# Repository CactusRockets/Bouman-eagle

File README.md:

# Avionics Boards for the Bouman-3KM Rocket

This repository contains the design files for the avionics boards used in the **Bouman 3 km rocket**, developed by **Cactus Rockets Design**.

## Description

The avionics system is composed of the following boards:

- **COTS Board**
- **Processing Board**
- **Actuation Board**
- **Battery Board**

The **COTS Board** is responsible for measuring pressure, altitude, acceleration, and the rocket’s orientation.

The **Processing Board** handles the processing of data received from the COTS board and the GPS module, stores this data, and transmits it via telemetry.

The **Actuation Board** contains the circuitry required to correctly activate the squibs (skibs) used in the recovery system.

The **Battery Board** distributes the battery voltages to connectors so they can be easily used by the other boards.

> **Note:** All board files can be opened using **Autodesk Eagle** software.

## Schematics and Layouts

### COTS Board

### Processing Board

### Actuation Board

### Battery Board

## System Operation

Both the **COTS Board** and the **Processing Board** include activation switches. The system startup sequence is as follows:

1. Activate the switch on the COTS Board.
2. Activate the switch on the Processing Board.

After each sensor reading, the data is stored on a microSD card and transmitted via telemetry.

When the COTS board detects the rocket’s descent, it sends a signal to the Actuation Board, which then triggers the squib responsible for deploying the **drogue parachute**.

During the descent with only the drogue parachute deployed, once the rocket reaches an altitude below **500 meters**, the system detects this condition and activates the second squib. This action deploys the **main parachute**, ensuring a stable and controlled descent of the rocket until touchdown.

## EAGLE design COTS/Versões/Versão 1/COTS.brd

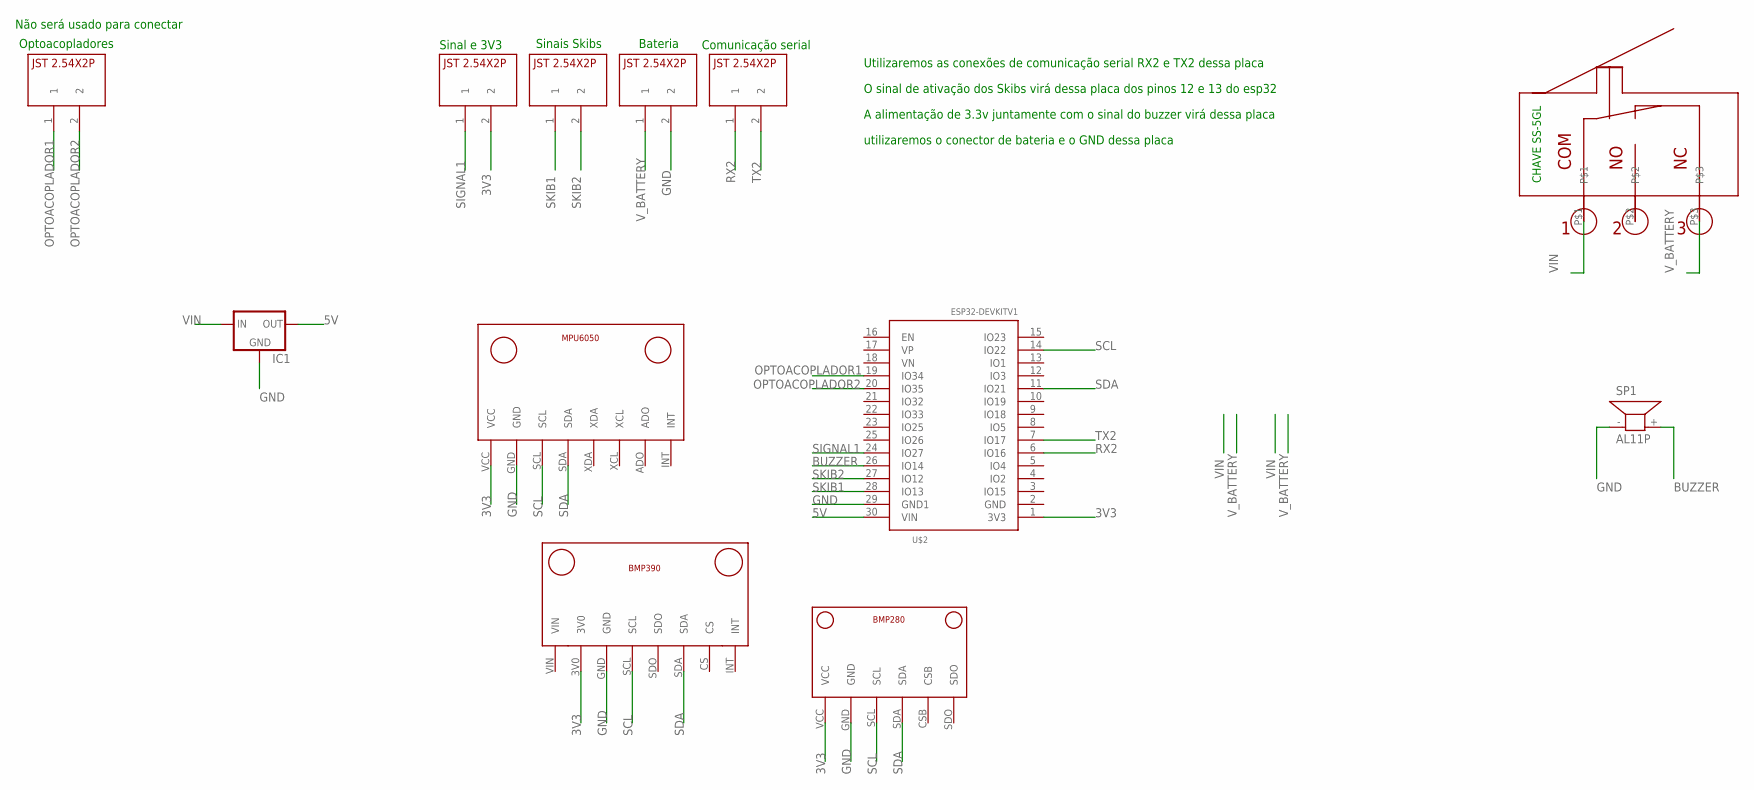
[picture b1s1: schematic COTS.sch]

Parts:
IC1: 78XXL
SP1: AL11P
U$1: MPU6050V1; MPU6050_FOOTPRINT
U$2: ESP32DEVKITV1; ESP32-DEVKITV1
U$3: BMP390V1; BMP390_FOOTPRINT
U$4, U$5, U$6, U$7, U$9: JST2.54X2P; JST2.54X2P_FOOTPRINT
U$8: CHAVE_SS-5GL; CHAVESS-5GL
U$10: BMP280V1; BMP280_FOOTPRINT

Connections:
3V3: U$1.VCC, U$2.1 (3V3), U$3.3V0, U$5.2, U$10.VCC
5V: IC1.OUT, U$2.30 (VIN)
BUZZER: SP1.+ (2), U$2.26 (IO14)
GND: IC1.GND, SP1.- (1), U$1.GND, U$2.29 (GND1), U$3.GND, U$6.2, U$10.GND
OPTOACOPLADOR1: U$2.19 (IO34), U$9.1
OPTOACOPLADOR2: U$2.20 (IO35), U$9.2
RX2: U$2.6 (IO16), U$7.1
SCL: U$1.SCL, U$2.14 (IO22), U$3.SCL, U$10.SCL
SDA: U$1.SDA, U$2.11 (IO21), U$3.SDA, U$10.SDA
SIGNAL1: U$2.24 (IO27), U$5.1
SKIB1: U$2.28 (IO13), U$4.1
SKIB2: U$2.27 (IO12), U$4.2
TX2: U$2.7 (IO17), U$7.2
VIN: IC1.IN, U$8.P$1
V_BATTERY: U$6.1, U$8.P$3

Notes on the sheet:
Sinais Skibs
Sinal e 3V3
Bateria
Comunicação serial
Optoacopladores
Utilizaremos as conexões de comunicação serial RX2 e TX2 dessa placa
O sinal de ativação dos Skibs virá dessa placa dos pinos 12 e 13 do esp32
A alimentação de 3.3v juntamente com o sinal do buzzer virá dessa placa
utilizaremos o conector de bateria e o GND dessa placa
Não será usado para conectar

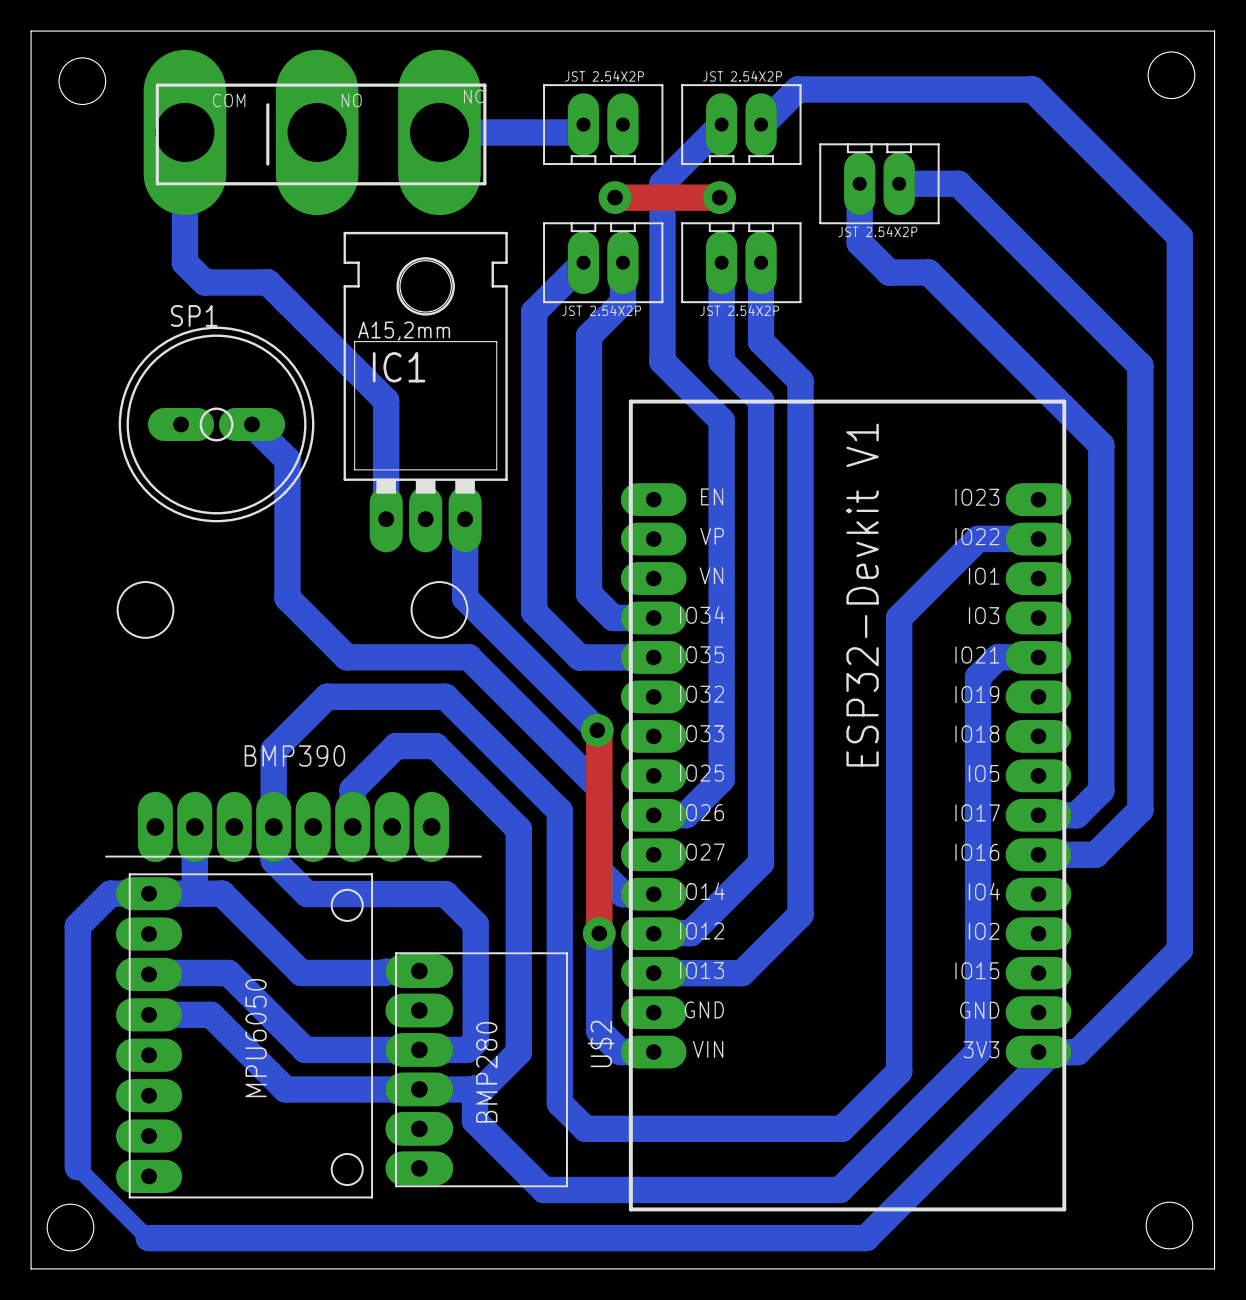
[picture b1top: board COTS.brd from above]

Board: 2 copper layers, 76.2 x 79.7 mm, 12 parts (0 on the bottom side), 15 nets.

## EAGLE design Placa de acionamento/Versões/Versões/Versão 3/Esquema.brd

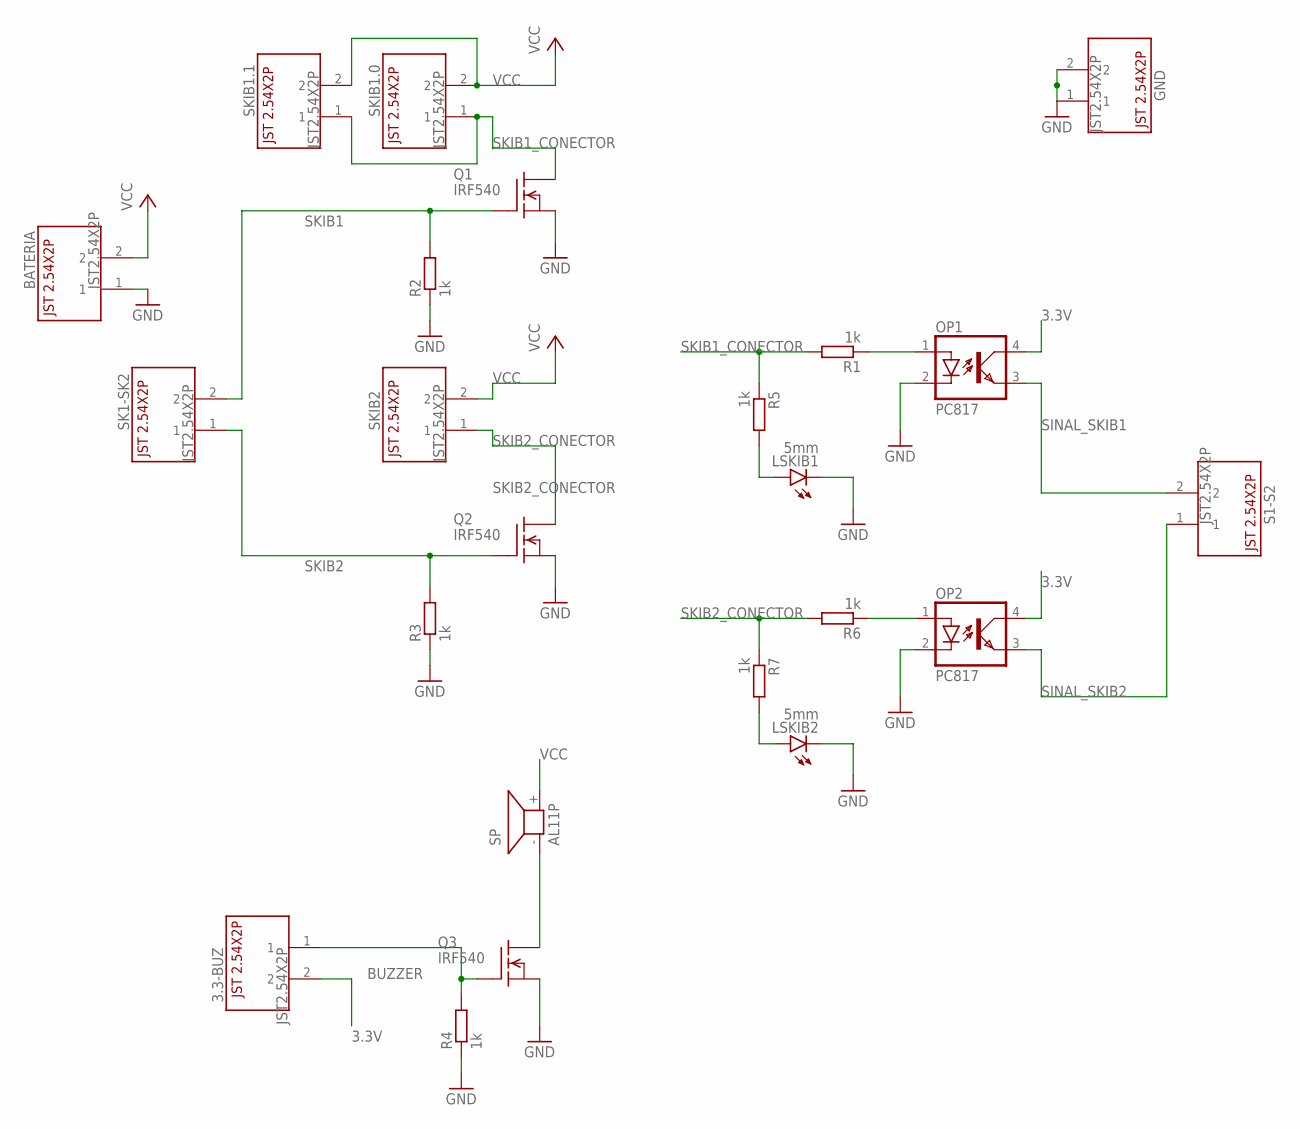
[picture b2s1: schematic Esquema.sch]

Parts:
3.3-BUZ: JST2.54X2P; JST2.54X2P_FOOTPRINT
BATERIA: JST2.54X2P; JST2.54X2P_FOOTPRINT
GND: JST2.54X2P; JST2.54X2P_FOOTPRINT
LSKIB1, LSKIB2: 5mm; LED5MM
OP1, OP2: PC817; DIL04
Q1, Q2, Q3: IRF540; TO220
R1, R2, R3, R4, R5, R6, R7: 1k; 0207/10
S1-S2: JST2.54X2P; JST2.54X2P_FOOTPRINT
SK1-SK2: JST2.54X2P; JST2.54X2P_FOOTPRINT
SKIB1.0, SKIB1.1, SKIB2: JST2.54X2P; JST2.54X2P_FOOTPRINT
SP: AL11P

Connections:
3.3V: 3.3-BUZ.2, OP1.4 (COL), OP2.4 (COL)
BUZZER: 3.3-BUZ.1, Q3.1 (G), R4.2
GND: BATERIA.1, GND.1, GND.2, LSKIB1.K (C), LSKIB2.K (C), OP1.2 (C), OP2.2 (C), Q1.3 (S), Q2.3 (S), Q3.3 (S), R2.1, R3.1, R4.1
unnamed: LSKIB2.A, R7.2
unnamed: Q3.2 (D), SP.- (1)
unnamed: LSKIB1.A, R5.2
unnamed: OP1.1 (A), R1.1
unnamed: OP2.1 (A), R6.1
SINAL_SKIB1: OP1.3 (EMIT), S1-S2.2
SINAL_SKIB2: OP2.3 (EMIT), S1-S2.1
SKIB1: Q1.1 (G), R2.2, SK1-SK2.2
SKIB1_CONECTOR: Q1.2 (D), R1.2, R5.1, SKIB1.0.1, SKIB1.1.1
SKIB2: Q2.1 (G), R3.2, SK1-SK2.1
SKIB2_CONECTOR: Q2.2 (D), R6.2, R7.1, SKIB2.1
VCC: BATERIA.2, SKIB1.0.2, SKIB1.1.2, SKIB2.2, SP.+ (2)

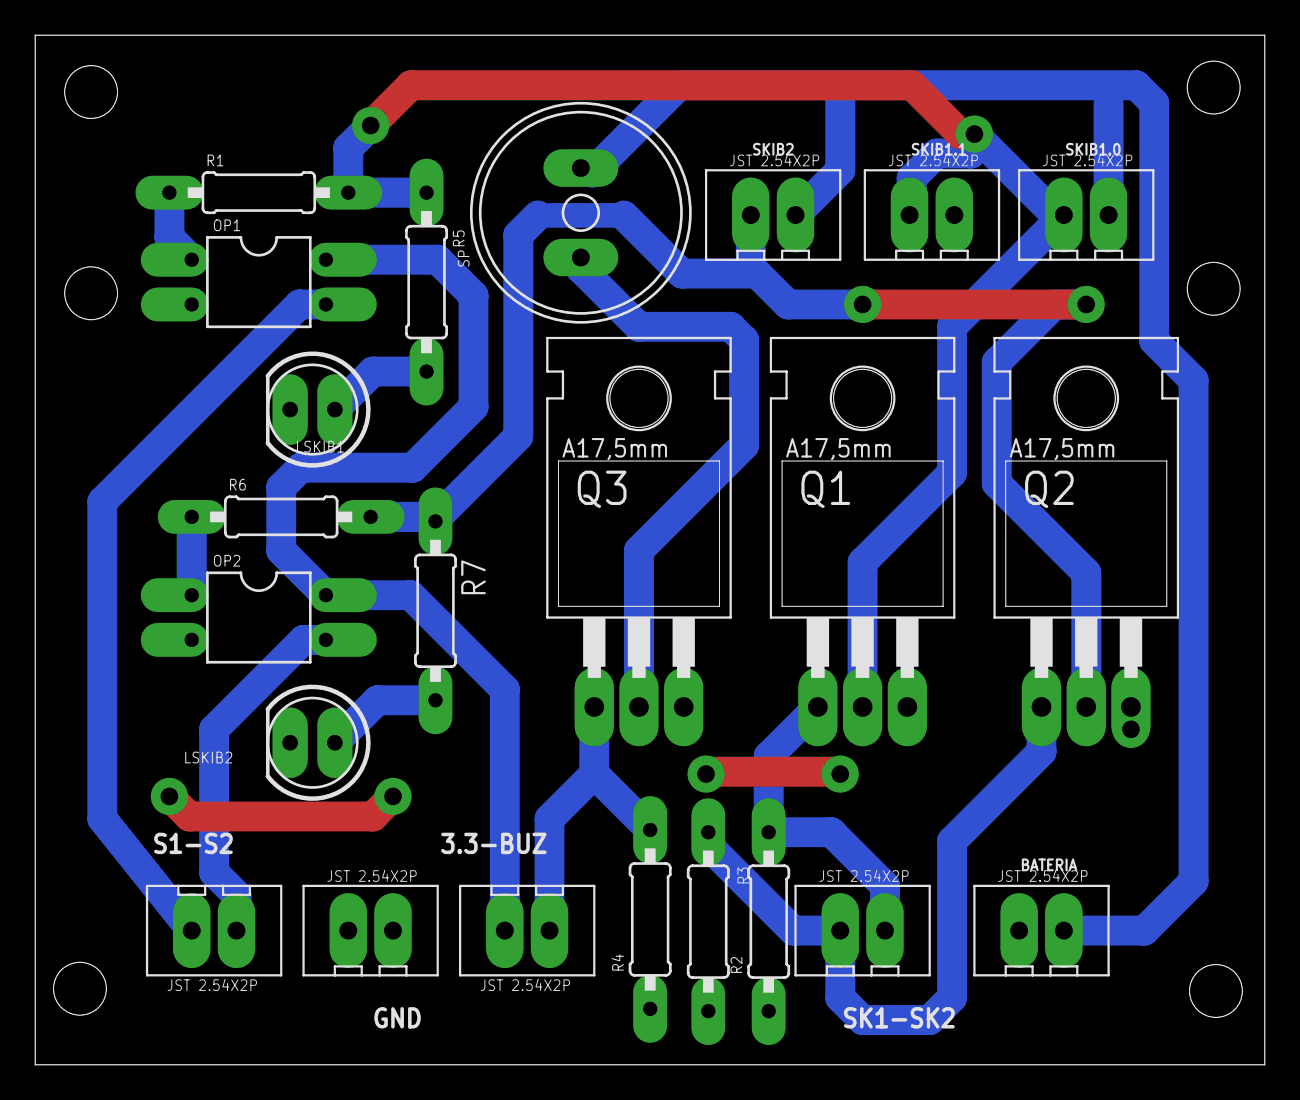
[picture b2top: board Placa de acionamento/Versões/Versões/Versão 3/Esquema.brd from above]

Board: 2 copper layers, 69.8 x 58.5 mm, 23 parts (0 on the bottom side), 15 nets.

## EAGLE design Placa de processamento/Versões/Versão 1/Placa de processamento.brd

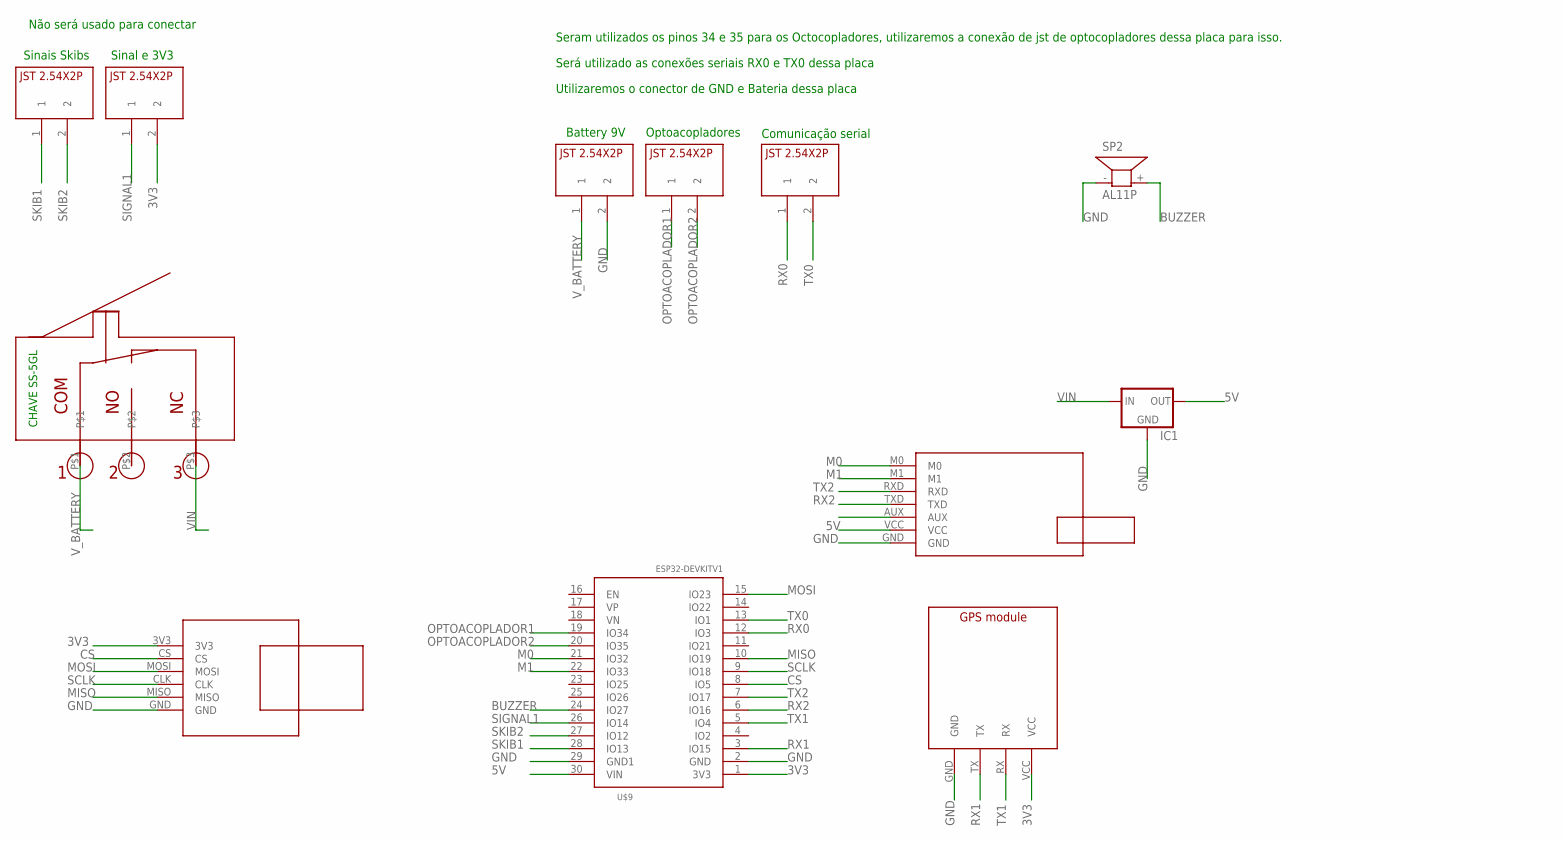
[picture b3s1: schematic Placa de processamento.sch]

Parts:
IC1: 78XXL
SP2: AL11P
U$2: MICROSD_SMALL_READER; MICROSD_SMALL_READER_FOOTPRINT
U$3, U$4, U$5, U$6, U$10: JST2.54X2P; JST2.54X2P_FOOTPRINT
U$7: GPS_MODULE; GPS_MODULE_FOOTPRINT
U$8: E22-400T30D; E22-400T30D_FOOTPRINT
U$9: ESP32DEVKITV1; ESP32-DEVKITV1
U$11: CHAVE_SS-5GL; CHAVESS-5GL

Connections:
3V3: U$2.3V3, U$5.2, U$7.VCC, U$9.1 (3V3)
5V: IC1.OUT, U$8.VCC, U$9.30 (VIN)
BUZZER: SP2.+ (2), U$9.24 (IO27)
CS: U$2.CS, U$9.8 (IO5)
GND: IC1.GND, SP2.- (1), U$2.GND, U$3.2, U$7.GND, U$8.GND, U$9.2 (GND), U$9.29 (GND1)
M0: U$8.M0, U$9.21 (IO32)
M1: U$8.M1, U$9.22 (IO33)
MISO: U$2.MISO, U$9.10 (IO19)
MOSI: U$2.MOSI, U$9.15 (IO23)
OPTOACOPLADOR1: U$6.1, U$9.19 (IO34)
OPTOACOPLADOR2: U$6.2, U$9.20 (IO35)
RX0: U$9.12 (IO3), U$10.1
RX1: U$7.TX, U$9.3 (IO15)
RX2: U$8.TXD, U$9.6 (IO16)
SCLK: U$2.CLK, U$9.9 (IO18)
SIGNAL1: U$5.1, U$9.26 (IO14)
SKIB1: U$4.1, U$9.28 (IO13)
SKIB2: U$4.2, U$9.27 (IO12)
TX0: U$9.13 (IO1), U$10.2
TX1: U$7.RX, U$9.5 (IO4)
TX2: U$8.RXD, U$9.7 (IO17)
VIN: IC1.IN, U$11.P$3
V_BATTERY: U$3.1, U$11.P$1

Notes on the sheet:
Battery 9V
Sinais Skibs
Sinal e 3V3
Optoacopladores
Comunicação serial
Seram utilizados os pinos 34 e 35 para os Octocopladores, utilizaremos a conexão de jst de optocopladores dessa placa para isso.
Será utilizado as conexões seriais RX0 e TX0 dessa placa
Utilizaremos o conector de GND e Bateria dessa placa
Não será usado para conectar

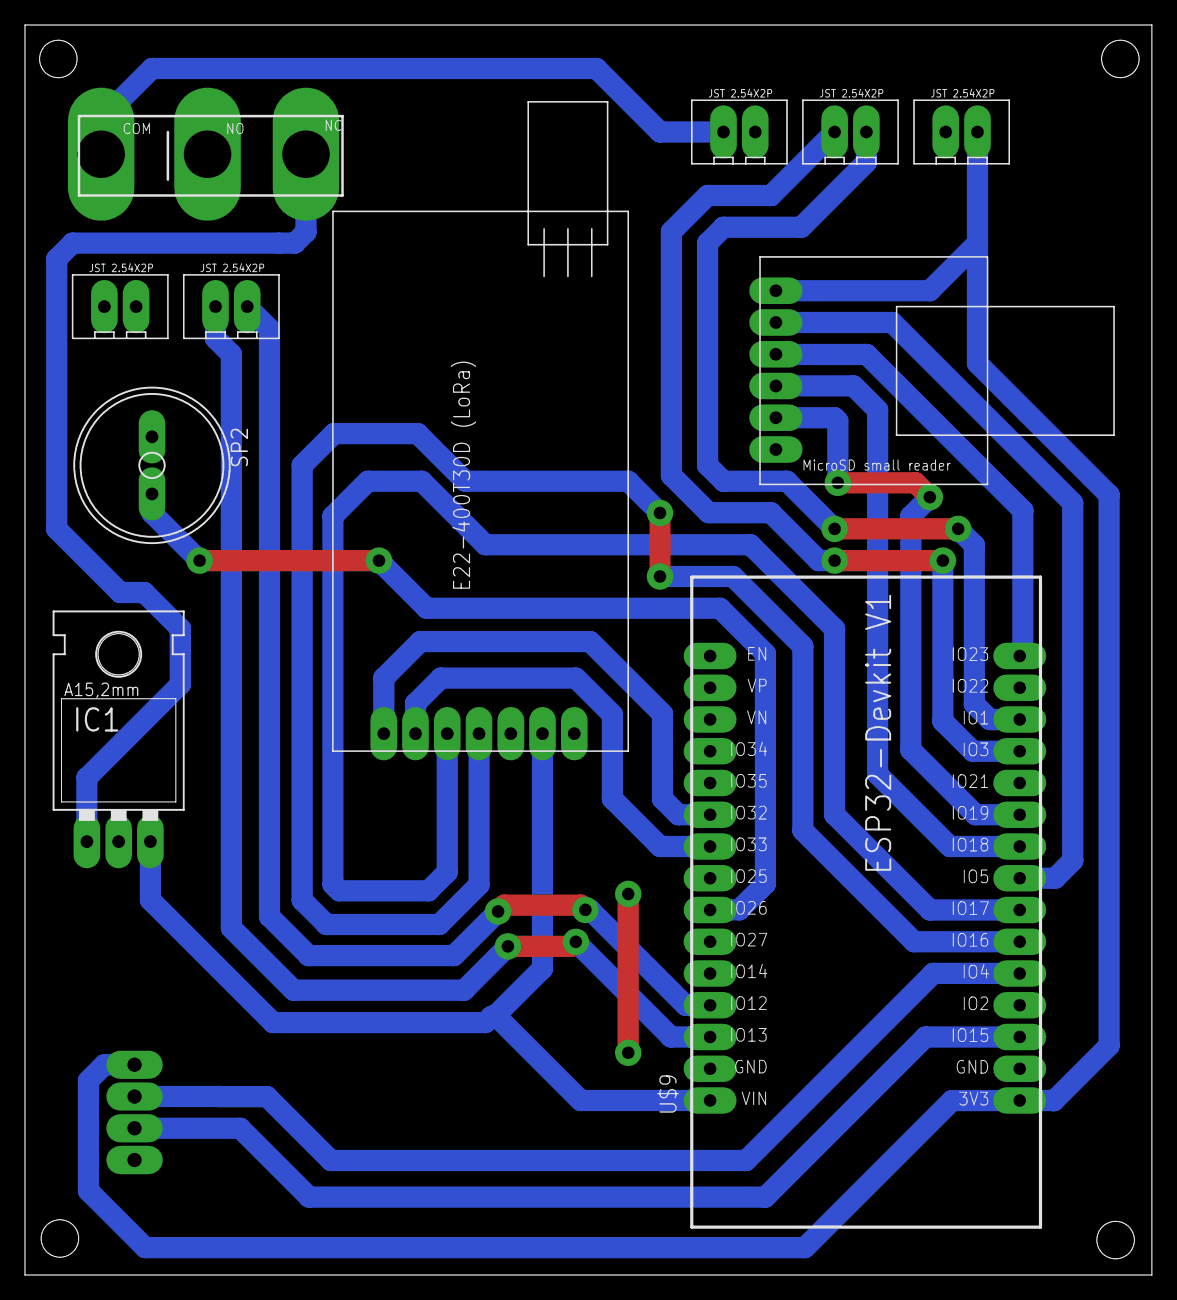
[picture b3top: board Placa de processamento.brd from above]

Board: 2 copper layers, 90.2 x 100.0 mm, 12 parts (1 on the bottom side), 23 nets.

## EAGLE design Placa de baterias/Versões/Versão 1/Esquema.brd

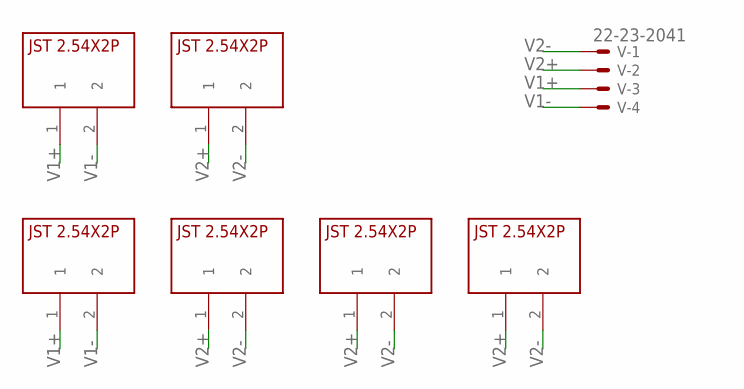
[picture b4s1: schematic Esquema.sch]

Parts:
U$1, U$2, U$3, U$4, U$5, U$6: JST2.54X2P; JST2.54X2P_FOOTPRINT
V: 22-23-2041

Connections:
V1+: U$1.1, U$4.1, V.3
V1-: U$1.2, U$4.2, V.4
V2+: U$2.1, U$3.1, U$5.1, U$6.1, V.2
V2-: U$2.2, U$3.2, U$5.2, U$6.2, V.1

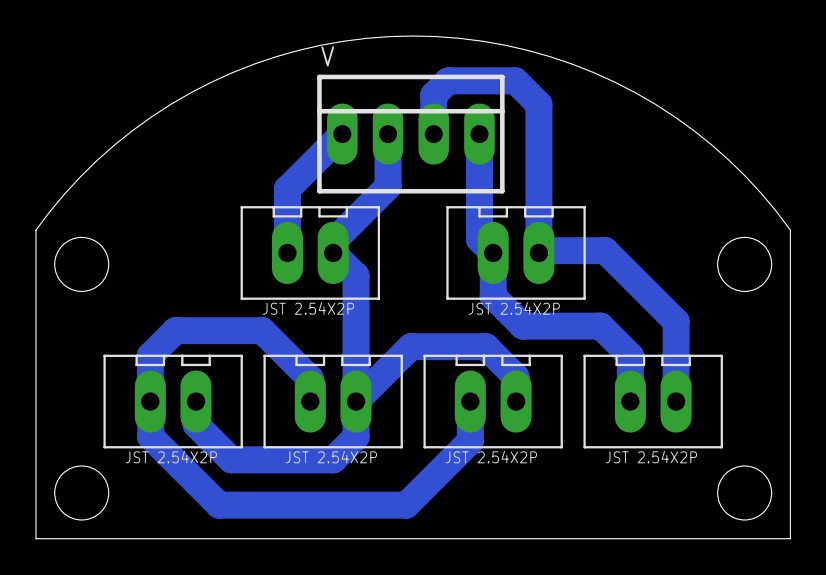
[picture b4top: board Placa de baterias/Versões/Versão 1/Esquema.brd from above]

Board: 2 copper layers, 41.9 x 27.9 mm, 7 parts (0 on the bottom side), 4 nets.

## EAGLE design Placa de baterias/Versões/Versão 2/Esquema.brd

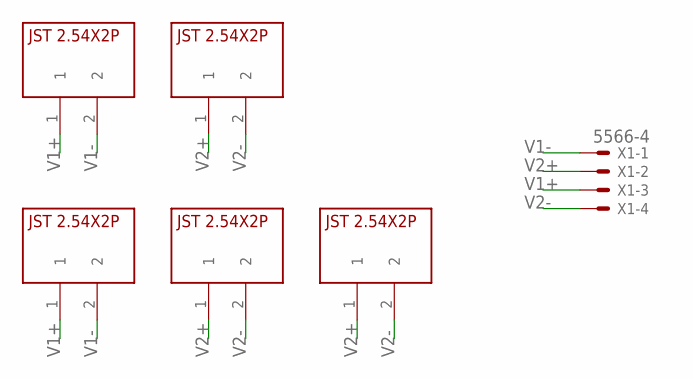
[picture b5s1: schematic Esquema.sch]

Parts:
U$1, U$2, U$3, U$4, U$5: JST2.54X2P; JST2.54X2P_FOOTPRINT
X1: 5566-4

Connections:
V1+: U$1.1, U$4.1, X1.3
V1-: U$1.2, U$4.2, X1.1
V2+: U$2.1, U$3.1, U$5.1, X1.2
V2-: U$2.2, U$3.2, U$5.2, X1.4

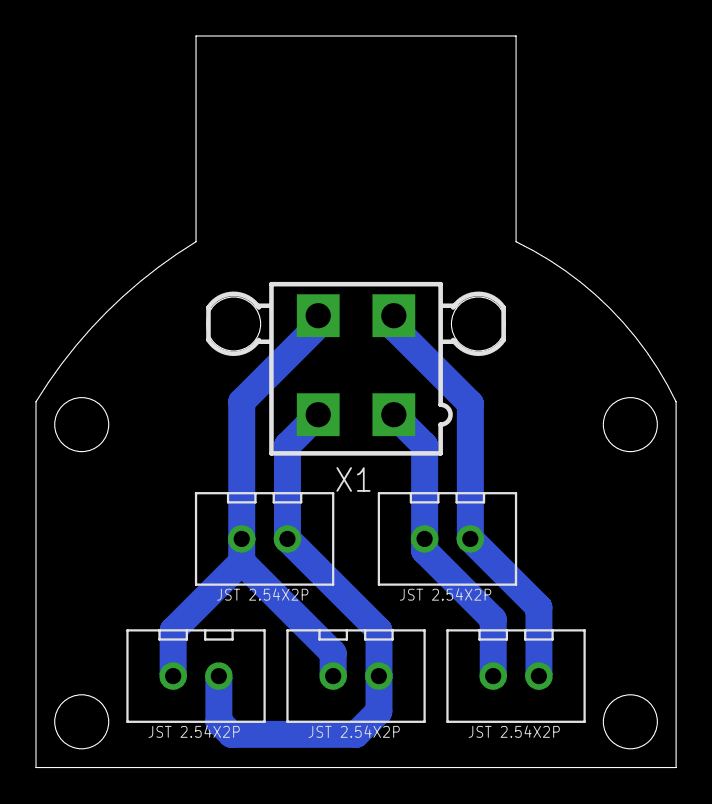
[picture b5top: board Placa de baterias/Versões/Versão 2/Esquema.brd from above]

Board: 2 copper layers, 35.6 x 40.6 mm, 6 parts (0 on the bottom side), 4 nets.

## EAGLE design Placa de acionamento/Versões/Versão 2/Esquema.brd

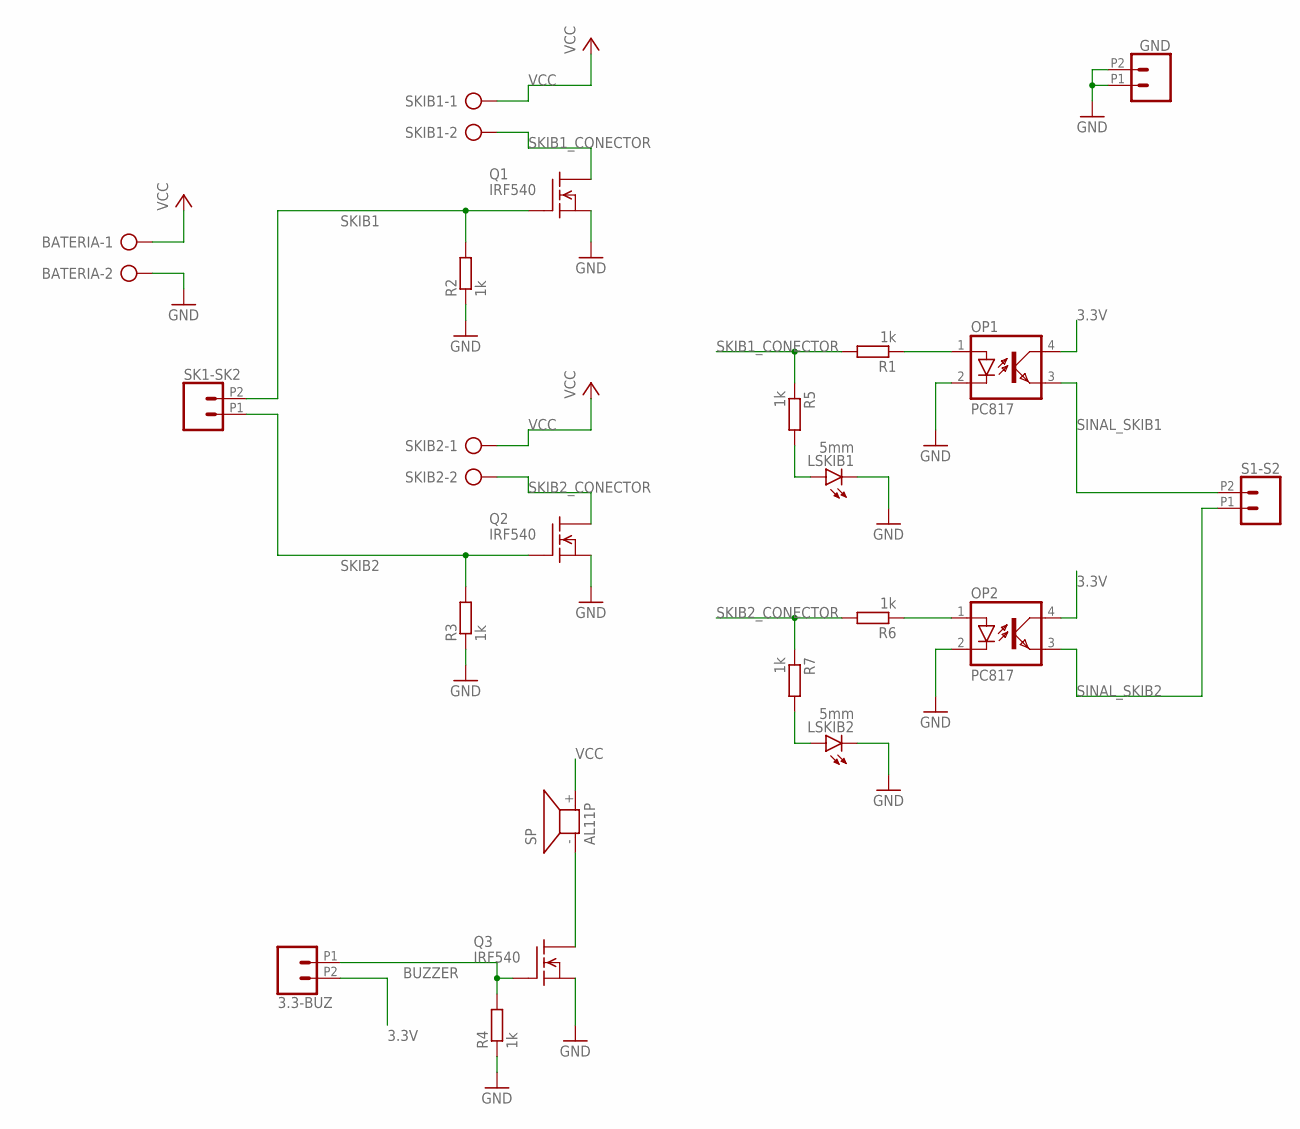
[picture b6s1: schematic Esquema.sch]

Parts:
3.3-BUZ: CONN_022.54MM_SCREWTERM; 1X02_2.54_SCREWTERM
BATERIA: AK500/2-H
GND: CONN_022.54MM_SCREWTERM; 1X02_2.54_SCREWTERM
LSKIB1, LSKIB2: 5mm; LED5MM
OP1, OP2: PC817; DIL04
Q1, Q2, Q3: IRF540; TO220
R1, R2, R3, R4, R5, R6, R7: 1k; 0207/10
S1-S2: CONN_022.54MM_SCREWTERM; 1X02_2.54_SCREWTERM
SK1-SK2: CONN_022.54MM_SCREWTERM; 1X02_2.54_SCREWTERM
SKIB1, SKIB2: AK500/2-H
SP: AL11P

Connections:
3.3V: 3.3-BUZ.P2 (2), OP1.4 (COL), OP2.4 (COL)
BUZZER: 3.3-BUZ.P1 (1), Q3.1 (G), R4.2
GND: BATERIA.2, GND.P1 (1), GND.P2 (2), LSKIB1.K (C), LSKIB2.K (C), OP1.2 (C), OP2.2 (C), Q1.3 (S), Q2.3 (S), Q3.3 (S), R2.1, R3.1, R4.1
unnamed: LSKIB2.A, R7.2
unnamed: Q3.2 (D), SP.- (1)
unnamed: LSKIB1.A, R5.2
unnamed: OP1.1 (A), R1.1
unnamed: OP2.1 (A), R6.1
SINAL_SKIB1: OP1.3 (EMIT), S1-S2.P2 (2)
SINAL_SKIB2: OP2.3 (EMIT), S1-S2.P1 (1)
SKIB1: Q1.1 (G), R2.2, SK1-SK2.P2 (2)
SKIB1_CONECTOR: Q1.2 (D), R1.2, R5.1, SKIB1.2
SKIB2: Q2.1 (G), R3.2, SK1-SK2.P1 (1)
SKIB2_CONECTOR: Q2.2 (D), R6.2, R7.1, SKIB2.2
VCC: BATERIA.1, SKIB1.1, SKIB2.1, SP.+ (2)

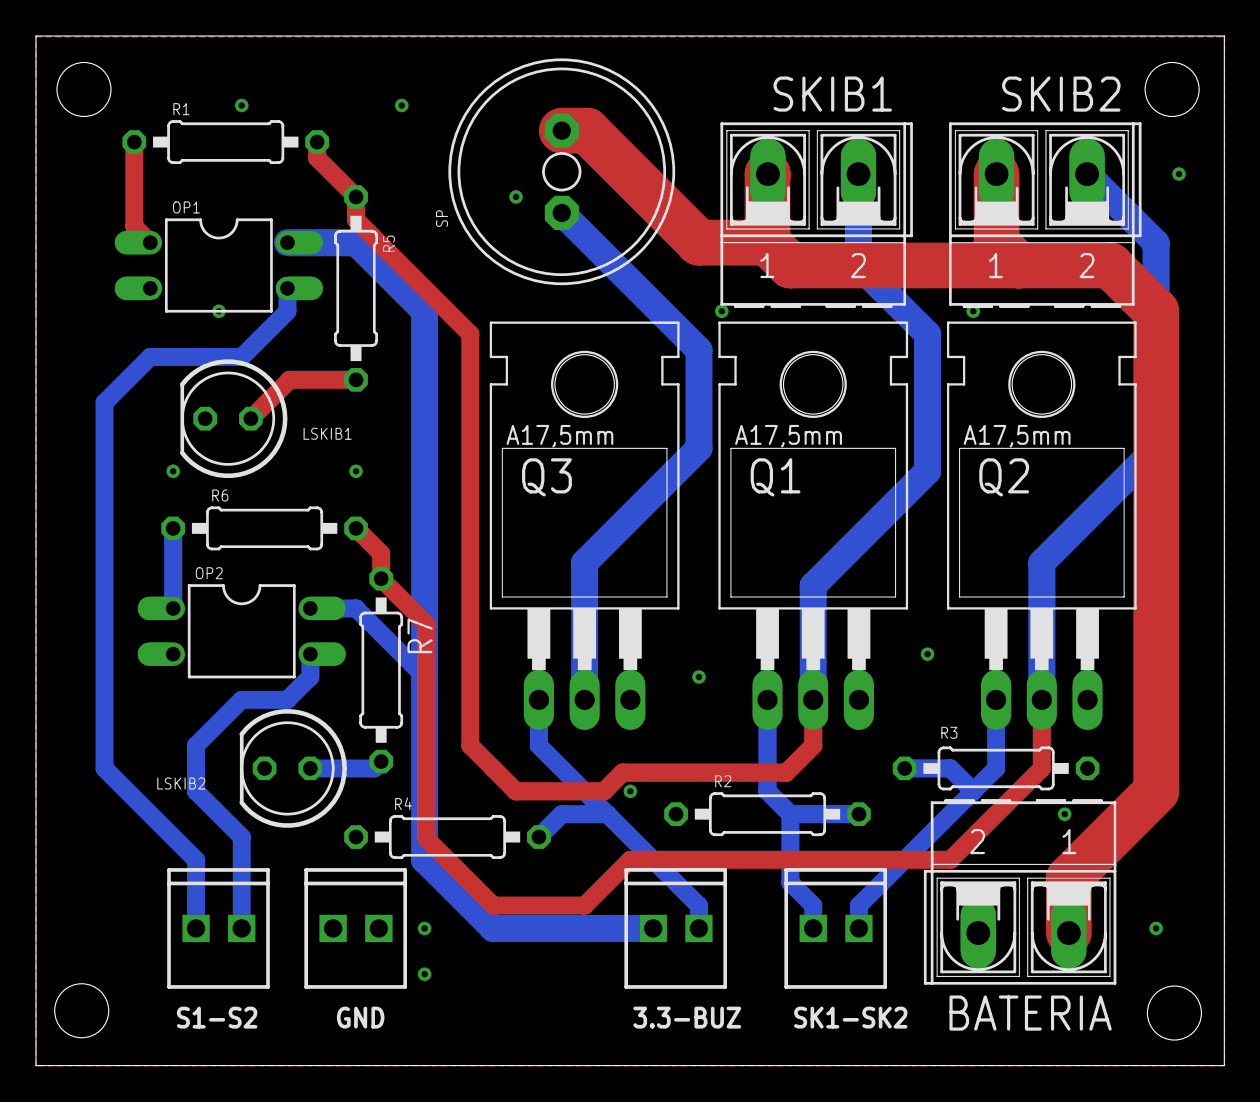
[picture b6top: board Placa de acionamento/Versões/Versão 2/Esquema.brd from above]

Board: 2 copper layers, 66.0 x 57.2 mm, 22 parts (0 on the bottom side), 15 nets.

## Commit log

2024-04-20 Upload para o Fusion
2024-04-20 Conexões em placa de processamento
2024-04-20 Começo do roteamento
2024-04-21 Update do roteamento
2024-04-21 Placas
2024-04-23 Atualização
2024-10-04 feat: ajustes na placa em conexões
2025-09-06 FEAT: adicionando versão 2 das placas
2025-09-06 CHORE: adicionando modelos 3D
2025-09-07 FEAT: adicionando regulador de tensao 5V
2025-09-08 Supostamente final com os modelos 3d corretos
2025-09-09 FIX: consertando chave de acionamento
2025-09-09 placa de baterias
2025-09-09 teste
2025-09-12 atualização placas
2025-09-17 CHORE: aplicando design rules da cactus
2025-09-18 CHORE: colocando pads ovais
2025-09-19 CHORE: adicionando pads ovais na placa de processamento
2025-09-24 CHORE: trocando conectores JST
2025-09-24 CHORE: adicionando pads ovais
2025-09-29 FIX: movendo LoRa para melhor posição
2025-09-30 Atualizando plata COTS
2025-09-30 Ajuste no 3D do BMP
    O BMP foi ajustado, para ficar posicionado na parte superior da placa
2025-10-28 placa de acionamento

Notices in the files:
parts and their libraries:
SparkFun-Connectors: Licensing: Creative Commons ShareAlike 4.0 International - https://creativecommons.org/licenses/by-sa/4.0
